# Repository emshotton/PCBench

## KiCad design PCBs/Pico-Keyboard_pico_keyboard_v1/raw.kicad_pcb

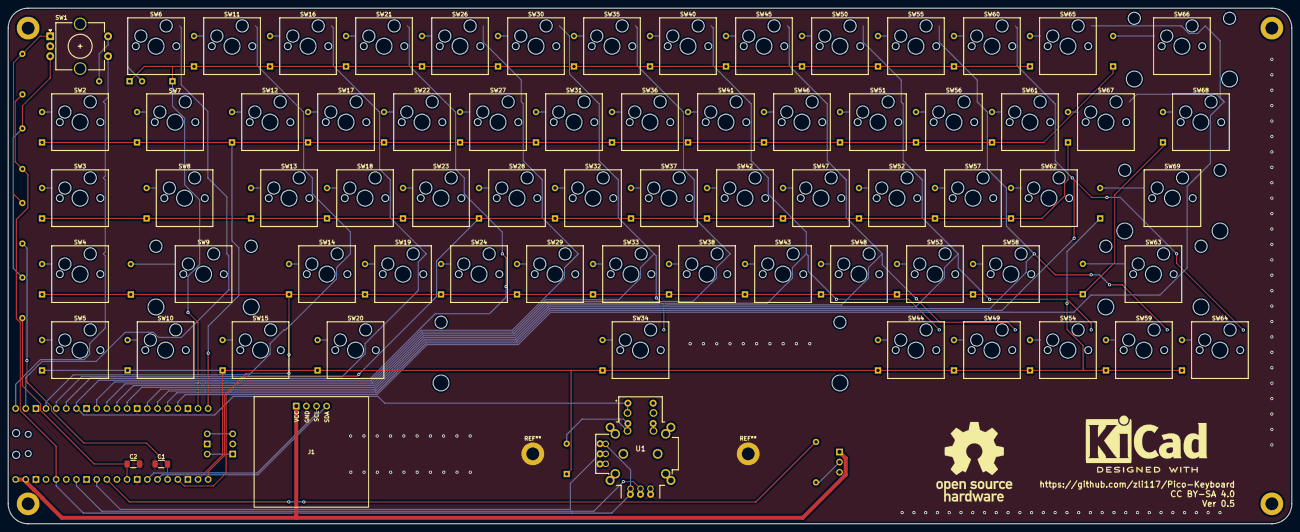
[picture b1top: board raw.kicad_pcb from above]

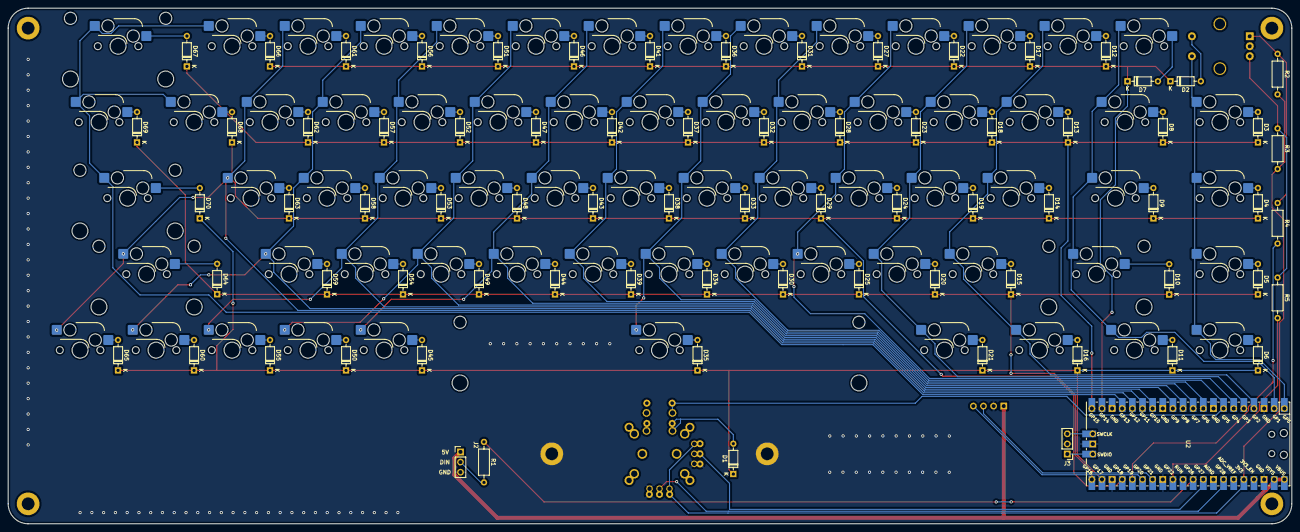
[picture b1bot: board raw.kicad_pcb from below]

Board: 2 copper layers, 321.8 x 129.2 mm, 147 parts (76 on the bottom side), 102 nets.

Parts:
C1, C2: 0.01 μF; C_1206_3216Metric_Pad1.33x1.80mm_HandSolder
D1, D2, D3, D4, D5, D6, D7, D8, D9, D10, D11, D12, D13, D14, D15, D16, D17, D18, D19, D20, D21, D22, D23, D24, D25, D27, D28, D29, D30, D31, D32, D33, D34, D35, D36, D37, D38, D39, D41, D42, D43, D44, D45, D46, D47, D48, D49, D50, D51, D52, D53, D54, D55, D56, D57, D58, D59, D60, D61, D62, D63, D64, D65, D66, D67, D68, D69, D70: D; D_DO-35_SOD27_P7.62mm_Horizontal
J1: Conn_01x04_12864; JMD0.96C
J2, J3: Conn_01x03_Female; PinHeader_1x03_P2.54mm_Vertical
R1: 330; R_Axial_DIN0207_L6.3mm_D2.5mm_P10.16mm_Horizontal
R2, R3, R4, R5: 10k; R_Axial_DIN0207_L6.3mm_D2.5mm_P10.16mm_Horizontal
SW1: RotaryEncoder_Switch; RotaryEncoder_Alps_EC11E-Switch_Vertical_H20mm_CircularMoun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
SW2: SW_esc; SW_Hotswap_Kailh_MX_1.00u
SW3: SW_del; SW_Hotswap_Kailh_MX_1.00u
SW4: SW_ins; SW_Hotswap_Kailh_MX_1.00u
SW5: SW_fn1; SW_Hotswap_Kailh_MX_1.00u
SW6: SW_`; SW_Hotswap_Kailh_MX_1.00u
SW7: SW_tab; SW_Hotswap_Kailh_MX_1.50u
SW8: SW_caps; SW_Hotswap_Kailh_MX_1.75u
SW9: SW_shift; SW_Hotswap_Kailh_MX_2.25u
SW10: SW_ctrl; SW_Hotswap_Kailh_MX_1.25u
SW11: SW_1; SW_Hotswap_Kailh_MX_1.00u
SW12: SW_q; SW_Hotswap_Kailh_MX_1.00u
SW13: SW_a; SW_Hotswap_Kailh_MX_1.00u
SW14: SW_z; SW_Hotswap_Kailh_MX_1.00u
SW15: SW_super; SW_Hotswap_Kailh_MX_1.25u
SW16: SW_2; SW_Hotswap_Kailh_MX_1.00u
SW17: SW_w; SW_Hotswap_Kailh_MX_1.00u
SW18: SW_s; SW_Hotswap_Kailh_MX_1.00u
SW19: SW_x; SW_Hotswap_Kailh_MX_1.00u
SW20: SW_alt; SW_Hotswap_Kailh_MX_1.25u
SW21: SW_3; SW_Hotswap_Kailh_MX_1.00u
SW22: SW_e; SW_Hotswap_Kailh_MX_1.00u
SW23: SW_d; SW_Hotswap_Kailh_MX_1.00u
SW24: SW_c; SW_Hotswap_Kailh_MX_1.00u
SW26: SW_4; SW_Hotswap_Kailh_MX_1.00u
SW27: SW_r; SW_Hotswap_Kailh_MX_1.00u
SW28: SW_f; SW_Hotswap_Kailh_MX_1.00u
SW29: SW_v; SW_Hotswap_Kailh_MX_1.00u
SW30: SW_5; SW_Hotswap_Kailh_MX_1.00u
SW31: SW_t; SW_Hotswap_Kailh_MX_1.00u
SW32: SW_g; SW_Hotswap_Kailh_MX_1.00u
SW33: SW_b; SW_Hotswap_Kailh_MX_1.00u
SW34: SW_space; SW_Hotswap_Kailh_MX_6.25u
SW35: SW_6; SW_Hotswap_Kailh_MX_1.00u
SW36: SW_y; SW_Hotswap_Kailh_MX_1.00u
SW37: SW_h; SW_Hotswap_Kailh_MX_1.00u
SW38: SW_n; SW_Hotswap_Kailh_MX_1.00u
SW40: SW_7; SW_Hotswap_Kailh_MX_1.00u
SW41: SW_u; SW_Hotswap_Kailh_MX_1.00u
SW42: SW_j; SW_Hotswap_Kailh_MX_1.00u
SW43: SW_m; SW_Hotswap_Kailh_MX_1.00u
SW44: SW_fn2; SW_Hotswap_Kailh_MX_1.00u
SW45: SW_8; SW_Hotswap_Kailh_MX_1.00u
SW46: SW_i; SW_Hotswap_Kailh_MX_1.00u
SW47: SW_k; SW_Hotswap_Kailh_MX_1.00u
SW48: SW_,; SW_Hotswap_Kailh_MX_1.00u
SW49: SW_left; SW_Hotswap_Kailh_MX_1.00u
SW50: SW_9; SW_Hotswap_Kailh_MX_1.00u
SW51: SW_o; SW_Hotswap_Kailh_MX_1.00u
SW52: SW_l; SW_Hotswap_Kailh_MX_1.00u
SW53: SW_.; SW_Hotswap_Kailh_MX_1.00u
SW54: SW_down; SW_Hotswap_Kailh_MX_1.00u
SW55: SW_0; SW_Hotswap_Kailh_MX_1.00u
SW56: SW_p; SW_Hotswap_Kailh_MX_1.00u
SW57: SW_;; SW_Hotswap_Kailh_MX_1.00u
SW58: SW_/; SW_Hotswap_Kailh_MX_1.00u
SW59: SW_up; SW_Hotswap_Kailh_MX_1.00u
SW60: SW_-; SW_Hotswap_Kailh_MX_1.00u
SW61: SW_[; SW_Hotswap_Kailh_MX_1.00u
SW62: SW_'; SW_Hotswap_Kailh_MX_1.00u
SW63: SW_r_shift; SW_Hotswap_Kailh_MX_2.75u
SW64: SW_right; SW_Hotswap_Kailh_MX_1.00u
SW65: SW_+; SW_Hotswap_Kailh_MX_1.00u
SW66: SW_back; SW_Hotswap_Kailh_MX_2.00u
SW67: SW_]; SW_Hotswap_Kailh_MX_1.00u
SW68: SW_\; SW_Hotswap_Kailh_MX_1.50u
SW69: SW_enter; SW_Hotswap_Kailh_MX_2.25u
U1: RKJXV1224; RKJXV122400R_COM09032
U2: Pico; RPi_Pico_SMD_TH

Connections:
+3V3: R2.2, R3.2, U1.A11 (V+), U1.B11 (H+), U2.36 (3V3)
+5V: J1.1, J2.1, U2.39 (VSYS), U2.40 (VBUS)
C0: SW1.S1, SW2.2 (B), SW3.2 (B), SW4.2 (B), SW5.2 (B), U2.1 (GPIO0)
C1: SW6.2 (B), SW7.2 (B), SW8.2 (B), SW9.2 (B), SW10.2 (B), U2.2 (GPIO1)
C2: SW11.2 (B), SW12.2 (B), SW13.2 (B), SW14.2 (B), SW15.2 (B), U2.4 (GPIO2)
C3: SW16.2 (B), SW17.2 (B), SW18.2 (B), SW19.2 (B), SW20.2 (B), U2.5 (GPIO3)
C4: SW21.2 (B), SW22.2 (B), SW23.2 (B), SW24.2 (B), U2.6 (GPIO4)
C5: SW26.2 (B), SW27.2 (B), SW28.2 (B), SW29.2 (B), U1.D1 (SEL-), U2.7 (GPIO5)
C6: SW30.2 (B), SW31.2 (B), SW32.2 (B), SW33.2 (B), SW34.2 (B), U2.9 (GPIO6)
C7: SW35.2 (B), SW36.2 (B), SW37.2 (B), SW38.2 (B), U2.10 (GPIO7)
C8: SW40.2 (B), SW41.2 (B), SW42.2 (B), SW43.2 (B), SW44.2 (B), U2.11 (GPIO8)
C9: SW45.2 (B), SW46.2 (B), SW47.2 (B), SW48.2 (B), SW49.2 (B), U2.12 (GPIO9)
C10: SW50.2 (B), SW51.2 (B), SW52.2 (B), SW53.2 (B), SW54.2 (B), U2.14 (GPIO10)
C11: SW55.2 (B), SW56.2 (B), SW57.2 (B), SW58.2 (B), SW59.2 (B), U2.15 (GPIO11)
C12: SW60.2 (B), SW61.2 (B), SW62.2 (B), SW63.2 (B), SW64.2 (B), U2.16 (GPIO12)
C13: SW65.2 (B), SW66.2 (B), SW67.2 (B), SW68.2 (B), SW69.2 (B), U2.17 (GPIO13)
GND: C1.1, C2.2, J1.2, J2.3, J3.2, SW1.C, U1.A13 (V-), U1.B13 (H-), U2.3 (GND), U2.8 (GND), U2.13 (GND), U2.18 (GND), U2.23 (GND), U2.28 (GND), U2.38 (GND), U2.42 (GND)
GPIO14: D2.1 (K), D7.1 (K), D12.1 (K), D17.1 (K), D22.1 (K), D27.1 (K), D31.1 (K), D36.1 (K), D41.1 (K), D46.1 (K), D51.1 (K), D56.1 (K), D61.1 (K), D66.1 (K), U2.19 (GPIO14)
GPIO15: D3.1 (K), D8.1 (K), D13.1 (K), D18.1 (K), D23.1 (K), D28.1 (K), D32.1 (K), D37.1 (K), D42.1 (K), D47.1 (K), D52.1 (K), D57.1 (K), D62.1 (K), D67.1 (K), U2.20 (GPIO15)
GPIO16: D5.1 (K), D10.1 (K), D15.1 (K), D20.1 (K), D25.1 (K), D30.1 (K), D34.1 (K), D39.1 (K), D44.1 (K), D49.1 (K), D54.1 (K), D59.1 (K), D64.1 (K), D69.1 (K), U2.21 (GPIO16)
GPIO17: D1.1 (K), D6.1 (K), D11.1 (K), D16.1 (K), D21.1 (K), D35.1 (K), D45.1 (K), D50.1 (K), D55.1 (K), D60.1 (K), D65.1 (K), D70.1 (K), U2.22 (GPIO17)
GPIO18: D4.1 (K), D9.1 (K), D14.1 (K), D19.1 (K), D24.1 (K), D29.1 (K), D33.1 (K), D38.1 (K), D43.1 (K), D48.1 (K), D53.1 (K), D58.1 (K), D63.1 (K), D68.1 (K), U2.24 (GPIO18)
GPIO19: C1.2, R4.2, U2.25 (GPIO19)
GPIO20: J1.4, U2.26 (GPIO20)
GPIO21: J1.3, U2.27 (GPIO21)
GPIO22: C2.1, R5.2, U2.29 (GPIO22)
GPIO26: R1.1, U2.31 (GPIO26_ADC0)
GPIO27: U1.A12 (V), U2.32 (GPIO27_ADC1)
GPIO28: U1.B12 (H), U2.34 (GPIO28_ADC2)
unnamed: D1.2 (A), U1.C1 (SEL+)
unnamed: D2.2 (A), SW1.S2
unnamed: D3.2 (A), SW2.1 (A)
unnamed: D4.2 (A), SW3.1 (A)
unnamed: D5.2 (A), SW4.1 (A)
unnamed: D6.2 (A), SW5.1 (A)
unnamed: D7.2 (A), SW6.1 (A)
unnamed: D8.2 (A), SW7.1 (A)
unnamed: D9.2 (A), SW8.1 (A)
unnamed: D10.2 (A), SW9.1 (A)
unnamed: D11.2 (A), SW10.1 (A)
unnamed: D12.2 (A), SW11.1 (A)
unnamed: D13.2 (A), SW12.1 (A)
unnamed: D14.2 (A), SW13.1 (A)
unnamed: D15.2 (A), SW14.1 (A)
unnamed: D16.2 (A), SW15.1 (A)
unnamed: D17.2 (A), SW16.1 (A)
unnamed: D18.2 (A), SW17.1 (A)
unnamed: D19.2 (A), SW18.1 (A)
unnamed: D20.2 (A), SW19.1 (A)
unnamed: D21.2 (A), SW20.1 (A)
unnamed: D22.2 (A), SW21.1 (A)
unnamed: D23.2 (A), SW22.1 (A)
unnamed: D24.2 (A), SW23.1 (A)
unnamed: D25.2 (A), SW24.1 (A)
unnamed: D27.2 (A), SW26.1 (A)
unnamed: D28.2 (A), SW27.1 (A)
unnamed: D29.2 (A), SW28.1 (A)
unnamed: D30.2 (A), SW29.1 (A)
unnamed: D31.2 (A), SW30.1 (A)
unnamed: D32.2 (A), SW31.1 (A)
unnamed: D33.2 (A), SW32.1 (A)
unnamed: D34.2 (A), SW33.1 (A)
unnamed: D35.2 (A), SW34.1 (A)
unnamed: D36.2 (A), SW35.1 (A)
unnamed: D37.2 (A), SW36.1 (A)
unnamed: D38.2 (A), SW37.1 (A)
unnamed: D39.2 (A), SW38.1 (A)
unnamed: D41.2 (A), SW40.1 (A)
unnamed: D42.2 (A), SW41.1 (A)
unnamed: D43.2 (A), SW42.1 (A)
unnamed: D44.2 (A), SW43.1 (A)
unnamed: D45.2 (A), SW44.1 (A)
unnamed: D46.2 (A), SW45.1 (A)
unnamed: D47.2 (A), SW46.1 (A)
unnamed: D48.2 (A), SW47.1 (A)
unnamed: D49.2 (A), SW48.1 (A)
unnamed: D50.2 (A), SW49.1 (A)
unnamed: D51.2 (A), SW50.1 (A)
unnamed: D52.2 (A), SW51.1 (A)
unnamed: D53.2 (A), SW52.1 (A)
unnamed: D54.2 (A), SW53.1 (A)
unnamed: D55.2 (A), SW54.1 (A)
unnamed: D56.2 (A), SW55.1 (A)
unnamed: D57.2 (A), SW56.1 (A)
unnamed: D58.2 (A), SW57.1 (A)
unnamed: D59.2 (A), SW58.1 (A)
unnamed: D60.2 (A), SW59.1 (A)
unnamed: D61.2 (A), SW60.1 (A)
unnamed: D62.2 (A), SW61.1 (A)
unnamed: D63.2 (A), SW62.1 (A)
unnamed: D64.2 (A), SW63.1 (A)
unnamed: D65.2 (A), SW64.1 (A)
unnamed: D66.2 (A), SW65.1 (A)
unnamed: D67.2 (A), SW66.1 (A)
unnamed: D68.2 (A), SW67.1 (A)
unnamed: D69.2 (A), SW68.1 (A)
unnamed: D70.2 (A), SW69.1 (A)
unnamed: J2.2, R1.2
unnamed: J3.1, U2.43 (SWDIO)
unnamed: J3.3, U2.41 (SWCLK)
unnamed: R2.1, R4.1, SW1.A
unnamed: R3.1, R5.1, SW1.B

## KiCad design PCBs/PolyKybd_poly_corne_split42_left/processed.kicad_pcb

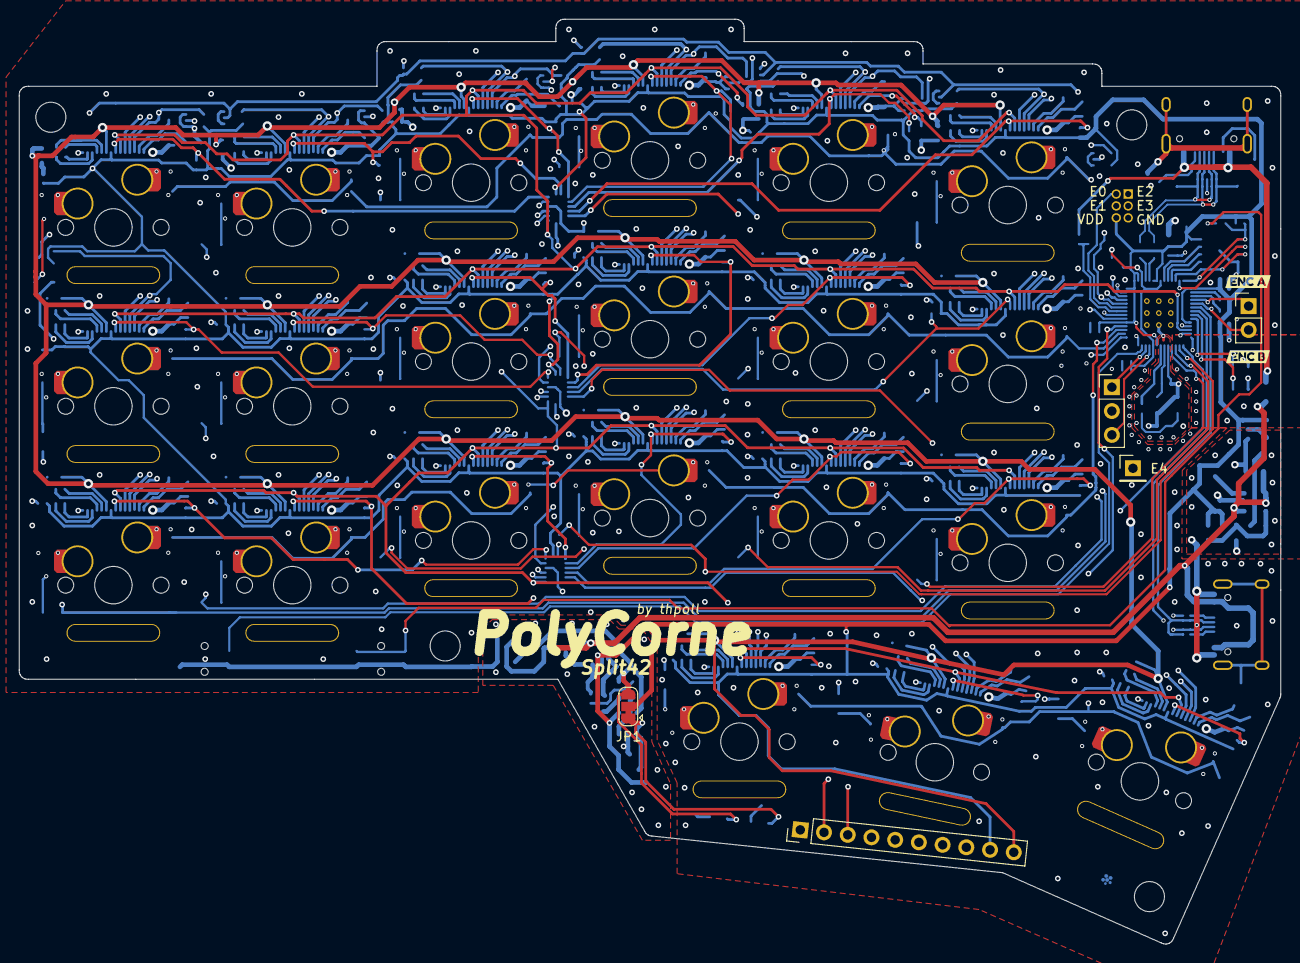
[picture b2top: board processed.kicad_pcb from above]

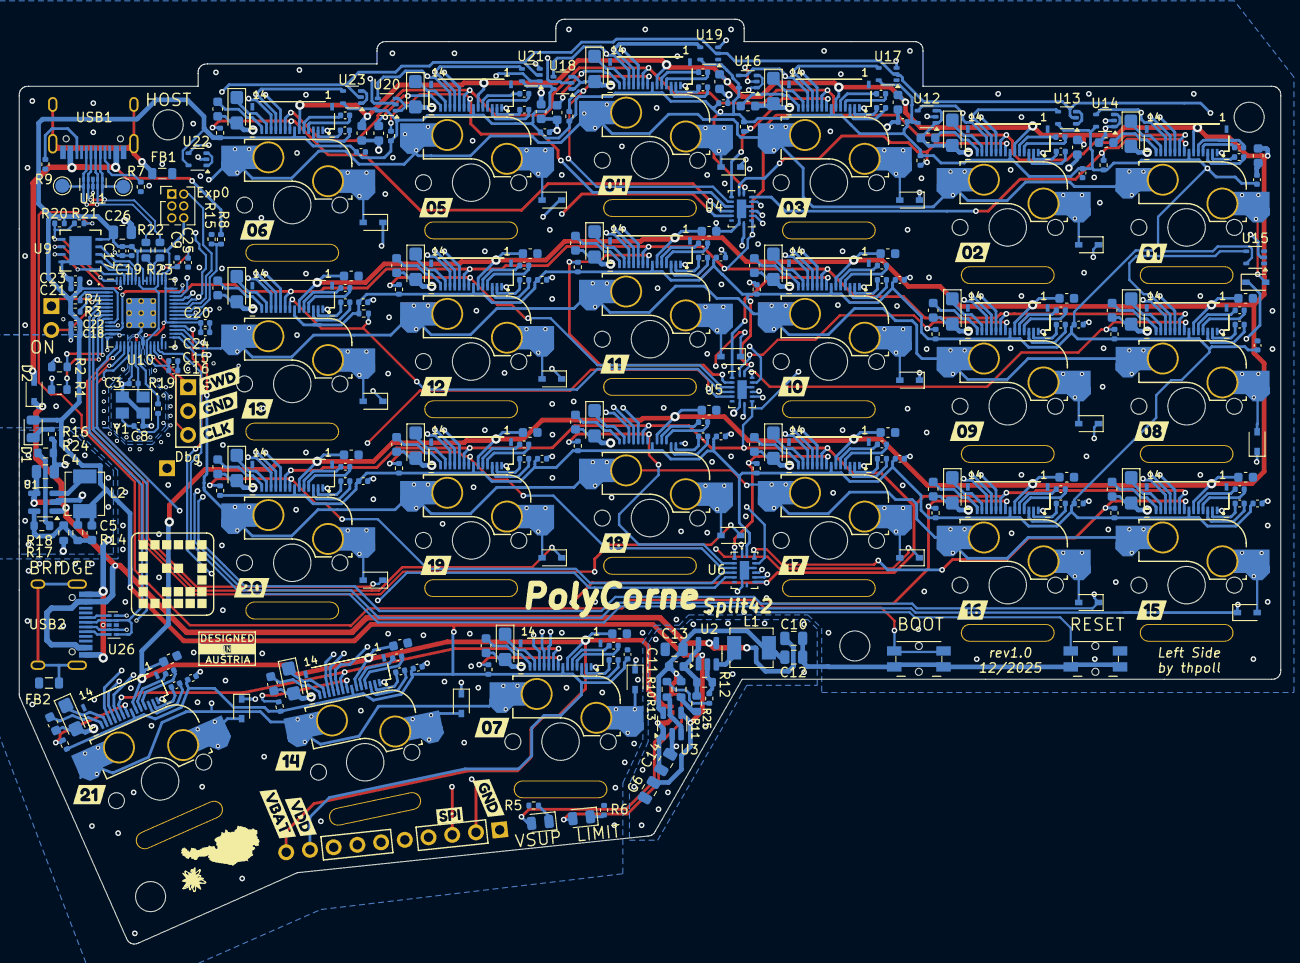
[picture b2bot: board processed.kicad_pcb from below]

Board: 4 copper layers, 134.3 x 98.5 mm, 330 parts (302 on the bottom side), 247 nets.

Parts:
C1_1, C1_2, C1_3, C1_4, C1_5, C1_6, C1_8, C1_9, C1_10, C1_11, C1_12, C1_13, C1_15, C1_16, C1_17, C1_18, C1_19, C1_20, C1_25, C1_26, C1_27: 2.2uF 0603 25V; C_0603_1608Metric
C2_1, C2_2, C2_3, C2_4, C2_5, C2_6, C2_8, C2_9, C2_10, C2_11, C2_12, C2_13, C2_15, C2_16, C2_17, C2_18, C2_19, C2_20, C2_25, C2_26, C2_27: 2.2uF 0603 16V; C_0603_1608Metric
C3, C8: 27pF 0402 16V; C_0402_1005Metric
C3_1, C3_2, C3_3, C3_4, C3_5, C3_6, C3_8, C3_9, C3_10, C3_11, C3_12, C3_13, C3_15, C3_16, C3_17, C3_18, C3_19, C3_20, C3_25, C3_26, C3_27, C5_1, C5_2, C5_3, C5_4, C5_5, C5_6, C5_8, C5_9, C5_10, C5_11, C5_12, C5_13, C5_15, C5_16, C5_17, C5_18, C5_19, C5_20, C5_25, C5_26, C5_27, C6_1, C6_2, C6_3, C6_4, C6_5, C6_6, C6_8, C6_9, C6_10, C6_11, C6_12, C6_13, C6_15, C6_16, C6_17, C6_18, C6_19, C6_20, C6_25, C6_26, C6_27, C24, C25: 1uF 0402 16V; C_0402_1005Metric
C4, C10: 4.7uF 0805 25V; C_0805_2012Metric
C4_1, C4_2, C4_3, C4_4, C4_5, C4_6, C4_8, C4_9, C4_10, C4_11, C4_12, C4_13, C4_15, C4_16, C4_17, C4_18, C4_19, C4_20, C4_25, C4_26, C4_27: 4.7uF 3216 25V Tantalum; CP_EIA-3216-18_Kemet-A
C5, C11: 6.8pF 0603 50V; C_0603_1608Metric
C6, C12, C13, C14, C26: 10uF 0805 16V; C_0805_2012Metric
C9, C15, C16, C17, C18, C19, C20, C21, C22, C23: 100nF 0402 16V; C_0402_1005Metric
D1: Red 0805 C84256; LED_0805_2012Metric
D1_1, D1_2, D1_3, D1_4, D1_5, D1_6, D1_8, D1_9, D1_10, D1_11, D1_12, D1_13, D1_15, D1_16, D1_17, D1_18, D1_19, D1_20, D1_25, D1_26, D1_27: 1N4148WSX; D_SOD-323Ext
D2: 1N5819WS; D_SOD-323Ext
D5: Green 0805 C2297; LED_0805_2012Metric
D6: Yellow 0805 C2296; LED_0805_2012Metric
DBG1: Conn_01x03_Male; PinHeader_1x03_P2.54mm_Vertical
DBG3: DebugPort; PinHeader_1x10_P2.54mm_Vertical
Enc0: Conn_01x02; PinHeader_1x02_P2.54mm_Vertical
Exp0: Conn_02x03; PinHeader_2x03_P1.27mm_Vertical
Exp1: Conn_01x01; PinHeader_1x01_P2.54mm_Vertical
FB1, FB2: GZ2012D601TF; L_0805_2012Metric
J1, J2, J3, J4, J5, J6, J8, J9, J10, J11, J12, J13, J15, J16, J17, J19, J20, J25, J26, J27: FH34SRJ-14S-0.5SH; FH34SRJ14S05SH50-Rev2
JP1: CurrentLimitBypass; SolderJumper-3_P1.3mm_Bridged12_RoundedPad1.0x1.5mm
L1, L2: 2.2uH; SMMS0420-2R2M
R1, R2: 22 0603; R_0603_1608Metric
R1_1, R1_2, R1_3, R1_4, R1_5, R1_6, R1_8, R1_9, R1_10, R1_11, R1_12, R1_13, R1_15, R1_16, R1_17, R1_18, R1_19, R1_20, R1_25, R1_26, R1_27, R15, R20, R25: 10k 0402; R_0402_1005Metric
R3, R4, R7, R9: 5.1K 0402; R_0402_1005Metric
R5, R6, R16, R19, R21: 1k 0402; R_0402_1005Metric
R8: 5.6K 0402; R_0402_1005Metric
R10, R11: 390k 0603 1%; R_0603_1608Metric
R12, R17: 150k 0603; R_0603_1608Metric
R13: 12k 0603; R_0603_1608Metric
R14: 680k 0603; R_0603_1608Metric
R18: 10M 0603; R_0603_1608Metric
R22, R23: 27 0603; R_0603_1608Metric
R24: 2M2 0603; R_0603_1608Metric
SW2, SW3: EVQPUC02K; Panasonic_EVQPUL_EVQPUC
SW_K_1, SW_K_2, SW_K_3, SW_K_4, SW_K_5, SW_K_6, SW_K_7, SW_K_8, SW_K_9, SW_K_10, SW_K_11, SW_K_12, SW_K_13, SW_K_14, SW_K_15, SW_K_16, SW_K_17, SW_K_18, SW_K_19, SW_K_20, SW_K_21: Kailh CPG151101S11-16; Kailh_socket_MX_Indicators
TP1: USB_D-; TestPoint_Pad_D1.5mm
TP14: USB_D+; TestPoint_Pad_D1.5mm
U1, U2: TLV62569DBVR; SOT-23-5
U3: SY6280AAC; SOT-23-5
U4, U5, U6: 74HC595BQ; Nexperia 74HC595BQ DHVQFN16
U9: W25Q64JVXGIM; DFN_XGIQ TR_WIN
U10: RP2040; RP2040-QFN-56
U11, U26: TPD4E05U06DQAR; USON-10
U12, U13, U14, U15, U16, U17, U18, U19, U20, U21, U22, U23: 74AHC1G125GW,125; SOT-353_SC-70-5_Slim
USB1, USB2: TYPE-C-31-M-12; HRO-TYPE-C-31-M-12-Assembly
Y1: 7M12000044; Crystal_SMD_3225-4Pin_3.2x2.5mm
kibuzzard-63EB51FD: G***; kibuzzard-63EB51FD
kibuzzard-639C2A93: G***; kibuzzard-639C2A93
kibuzzard-639C2D09: G***; kibuzzard-639C2D09
kibuzzard-639C2D25: G***; kibuzzard-639C2D25
kibuzzard-639C28BB, kibuzzard-639C28BB#2: G***; kibuzzard-639C28BB
kibuzzard-639C28CF: G***; kibuzzard-639C28CF
kibuzzard-639C34D4: G***; kibuzzard-639C34D4
kibuzzard-639C34FD: G***; kibuzzard-639C34FD
kibuzzard-639C35A2: G***; kibuzzard-639C35A2
kibuzzard-639C35AF: G***; kibuzzard-639C35AF
kibuzzard-639C35B8: G***; kibuzzard-639C35B8
kibuzzard-639C35C3: G***; kibuzzard-639C35C3
kibuzzard-639C35CB: G***; kibuzzard-639C35CB
kibuzzard-639C35DA: G***; kibuzzard-639C35DA
kibuzzard-639C35E7: G***; kibuzzard-639C35E7
kibuzzard-639C39A5: G***; kibuzzard-639C39A5
kibuzzard-639C294B: G***; kibuzzard-639C294B
kibuzzard-639C352E: G***; kibuzzard-639C352E
kibuzzard-639C353A: G***; kibuzzard-639C353A
kibuzzard-639C355D: G***; kibuzzard-639C355D
kibuzzard-639C357F: G***; kibuzzard-639C357F
kibuzzard-639C358A: G***; kibuzzard-639C358A
kibuzzard-639C3508: G***; kibuzzard-639C3508
kibuzzard-639C3514: G***; kibuzzard-639C3514
kibuzzard-639C3522: G***; kibuzzard-639C3522
kibuzzard-639C3548: G***; kibuzzard-639C3548
kibuzzard-639C3550: G***; kibuzzard-639C3550
kibuzzard-639C3575: G***; kibuzzard-639C3575
kibuzzard-639C3594: G***; kibuzzard-639C3594

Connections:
+1V1: C15.1, C16.1, C25.1, U10.23 (DVDD), U10.45 (VREG_VOUT), U10.50 (DVDD)
/K_1/C1N: C6_2.2, J2.5
/K_1/C1P: C6_2.1, J2.4
/K_1/C2N: C5_2.2, J2.3
/K_1/C2P: C5_2.1, J2.2
/K_1/CS: J2.8, R1_2.2, U4.1 (QB)
/K_1/VCC: C1_2.1, J2.14
/K_1/VCOMH: C4_2.1, J2.13
/K_2/C1N: C6_3.2, J3.5
/K_2/C1P: C6_3.1, J3.4
/K_2/C2N: C5_3.2, J3.3
/K_2/C2P: C5_3.1, J3.2
/K_2/CS: J3.8, R1_3.2, U4.2 (QC)
/K_2/VCC: C1_3.1, J3.14
/K_2/VCOMH: C4_3.1, J3.13
/K_3/C1N: C6_4.2, J4.5
/K_3/C1P: C6_4.1, J4.4
/K_3/C2N: C5_4.2, J4.3
/K_3/C2P: C5_4.1, J4.2
/K_3/CS: J4.8, R1_4.2, U4.3 (QD)
/K_3/VCC: C1_4.1, J4.14
/K_3/VCOMH: C4_4.1, J4.13
/K_4/C1N: C6_5.2, J5.5
/K_4/C1P: C6_5.1, J5.4
/K_4/C2N: C5_5.2, J5.3
/K_4/C2P: C5_5.1, J5.2
/K_4/CS: J5.8, R1_5.2, U4.4 (QE)
/K_4/VCC: C1_5.1, J5.14
/K_4/VCOMH: C4_5.1, J5.13
/K_5/C1N: C6_6.2, J6.5
/K_5/C1P: C6_6.1, J6.4
/K_5/C2N: C5_6.2, J6.3
/K_5/C2P: C5_6.1, J6.2
/K_5/CS: J6.8, R1_6.2, U4.5 (QF)
/K_5/VCC: C1_6.1, J6.14
/K_5/VCOMH: C4_6.1, J6.13
/K_A/C1N: C6_16.2, J16.5
/K_A/C1P: C6_16.1, J16.4
/K_A/C2N: C5_16.2, J16.3
/K_A/C2P: C5_16.1, J16.2
/K_A/CS: J16.8, R1_16.2, U6.1 (QB)
/K_A/VCC: C1_16.1, J16.14
/K_A/VCOMH: C4_16.1, J16.13
/K_B/C1N: C6_27.2, J27.5
/K_B/C1P: C6_27.1, J27.4
/K_B/C2N: C5_27.2, J27.3
/K_B/C2P: C5_27.1, J27.2
/K_B/CS: J27.8, R1_27.2, U6.6 (QG)
/K_B/VCC: C1_27.1, J27.14
/K_B/VCOMH: C4_27.1, J27.13
/K_C/C1N: C6_25.2, J25.5
/K_C/C1P: C6_25.1, J25.4
/K_C/C2N: C5_25.2, J25.3
/K_C/C2P: C5_25.1, J25.2
/K_C/CS: J25.8, R1_25.2, U4.6 (QG)
/K_C/VCC: C1_25.1, J25.14
/K_C/VCOMH: C4_25.1, J25.13
/K_D/CS: R1_18.2, U6.3 (QD)
/K_E/C1N: C6_11.2, J11.5
/K_E/C1P: C6_11.1, J11.4
/K_E/C2N: C5_11.2, J11.3
/K_E/C2P: C5_11.1, J11.2
/K_E/CS: J11.8, R1_11.2, U5.3 (QD)
/K_E/VCC: C1_11.1, J11.14
/K_E/VCOMH: C4_11.1, J11.13
/K_F/C1N: C6_19.2, J19.5
/K_F/C1P: C6_19.1, J19.4
/K_F/C2N: C5_19.2, J19.3
/K_F/C2P: C5_19.1, J19.2
/K_F/CS: J19.8, R1_19.2, U6.4 (QE)
/K_F/VCC: C1_19.1, J19.14
/K_F/VCOMH: C4_19.1, J19.13
/K_G/C1N: C6_20.2, J20.5
/K_G/C1P: C6_20.1, J20.4
/K_G/C2N: C5_20.2, J20.3
/K_G/C2P: C5_20.1, J20.2
/K_G/CS: J20.8, R1_20.2, U6.5 (QF)
/K_G/VCC: C1_20.1, J20.14
/K_G/VCOMH: C4_20.1, J20.13
/K_L1/C1N: C6_1.2, J1.5
/K_L1/C1P: C6_1.1, J1.4
/K_L1/C2N: C5_1.2, J1.3
/K_L1/C2P: C5_1.1, J1.2
/K_L1/CS: J1.8, R1_1.2, U4.15 (QA)
/K_L1/VCC: C1_1.1, J1.14
/K_L1/VCOMH: C4_1.1, J1.13
/K_L2/C1N: C6_8.2, J8.5
/K_L2/C1P: C6_8.1, J8.4
/K_L2/C2N: C5_8.2, J8.3
/K_L2/C2P: C5_8.1, J8.2
/K_L2/CS: J8.8, R1_8.2, U5.15 (QA)
/K_L2/VCC: C1_8.1, J8.14
/K_L2/VCOMH: C4_8.1, J8.13
/K_L3/C1N: C6_15.2, J15.5
/K_L3/C1P: C6_15.1, J15.4
/K_L3/C2N: C5_15.2, J15.3
/K_L3/C2P: C5_15.1, J15.2
/K_L3/CS: J15.8, R1_15.2, U6.15 (QA)
/K_L3/VCC: C1_15.1, J15.14
/K_L3/VCOMH: C4_15.1, J15.13
/K_Q/C1N: C6_9.2, J9.5
/K_Q/C1P: C6_9.1, J9.4
/K_Q/C2N: C5_9.2, J9.3
/K_Q/C2P: C5_9.1, J9.2
/K_Q/CS: J9.8, R1_9.2, U5.1 (QB)
/K_Q/VCC: C1_9.1, J9.14
/K_Q/VCOMH: C4_9.1, J9.13
/K_R/C1N: C6_12.2, J12.5
/K_R/C1P: C6_12.1, J12.4
/K_R/C2N: C5_12.2, J12.3
/K_R/C2P: C5_12.1, J12.2
/K_R/CS: J12.8, R1_12.2, U5.4 (QE)
/K_R/VCC: C1_12.1, J12.14
/K_R/VCOMH: C4_12.1, J12.13
/K_S/C1N: C6_17.2, J17.5
/K_S/C1P: C6_17.1, J17.4
/K_S/C2N: C5_17.2, J17.3
/K_S/C2P: C5_17.1, J17.2
/K_S/CS: J17.8, R1_17.2, U6.2 (QC)
/K_S/VCC: C1_17.1, J17.14
/K_S/VCOMH: C4_17.1, J17.13
/K_T/C1N: C6_13.2, J13.5
/K_T/C1P: C6_13.1, J13.4
/K_T/C2N: C5_13.2, J13.3
/K_T/C2P: C5_13.1, J13.2
/K_T/CS: J13.8, R1_13.2, U5.5 (QF)
/K_T/VCC: C1_13.1, J13.14
/K_T/VCOMH: C4_13.1, J13.13
/K_V/C1N: C6_26.2, J26.5
/K_V/C1P: C6_26.1, J26.4
/K_V/C2N: C5_26.2, J26.3
/K_V/C2P: C5_26.1, J26.2
/K_V/CS: J26.8, R1_26.2, U5.6 (QG)
/K_V/VCC: C1_26.1, J26.14
/K_V/VCOMH: C4_26.1, J26.13
/K_W/C1N: C6_10.2, J10.5
/K_W/C1P: C6_10.1, J10.4
/K_W/C2N: C5_10.2, J10.3
/K_W/C2P: C5_10.1, J10.2
/K_W/CS: J10.8, R1_10.2, U5.2 (QC)
/K_W/VCC: C1_10.1, J10.14
/K_W/VCOMH: C4_10.1, J10.13
/RpPico/GPIO6: R1.1, U10.8 (GPIO6)
/RpPico/GPIO7: R2.1, U10.9 (GPIO7)
/RpPico/GPIO24: R8.2, R15.1, U10.36 (GPIO24)
/RpPico/QSPI_SCLK: U9.6 (CLK), U10.52 (QSPI_SCLK)
/RpPico/QSPI_SD0: U9.5 (DI(IO0)), U10.53 (QSPI_SD0)
/RpPico/QSPI_SD1: U9.2 (DO(IO1)), U10.55 (QSPI_SD1)
/RpPico/QSPI_SD2: U9.3 (~WP(IO2)), U10.54 (QSPI_SD2)
/RpPico/QSPI_SD3: U9.7 (~HOLD_OR_RESET_(IO3)), U10.51 (QSPI_SD3)
/RpPico/QSPI_SS: R20.2, R21.1, U9.1 (~CS), U10.56 (QSPI_SS)
/RpPico/RUN: SW3.2, U10.26 (RUN)
/RpPico/SWCLK: DBG1.3, U10.24 (SWCLK)
/RpPico/SWD: DBG1.1, U10.25 (SWD)
/RpPico/USB_D+: R22.1, TP14.1, U11.1 (IO1), U11.4 (D2+), U11.7 (NC), U11.10 (NC), USB1.6 (DP1), USB1.8 (DP2)
/RpPico/USB_D-: R23.1, TP1.1, U11.2 (IO2), U11.5 (D2-), U11.6 (NC), U11.9 (NC), USB1.5 (DN2), USB1.7 (DN1)
/RpPico/XIN: C3.2, U10.20 (XIN), Y1.1
/RpPico/XOUT: R19.2, U10.21 (XOUT)
/RpPico/~USB_BOOT: R21.2, SW2.2
/SCLK1: J1.11, J8.11, J15.11, U15.4 (B)
/SCLK2: J2.11, J9.11, J16.11, U13.4 (B)
/SCLK3: J3.11, J10.11, J17.11, U17.4 (B)
/SCLK4: J4.11, J11.11, J25.11, U19.4 (B)
/SCLK5: J5.11, J12.11, J19.11, J26.11, U21.4 (B)
/SCLK6: J6.11, J13.11, J20.11, J27.11, U23.4 (B)
/SDIN1: J1.12, J8.12, J15.12, U14.4 (B)
/SDIN2: J2.12, J9.12, J16.12, U12.4 (B)
/SDIN3: J3.12, J10.12, J17.12, U16.4 (B)
/SDIN4: J4.12, J11.12, J25.12, U18.4 (B)
/SDIN5: J5.12, J12.12, J19.12, J26.12, U20.4 (B)
/SDIN6: J6.12, J13.12, J20.12, J27.12, U22.4 (B)
/ShiftRegisters/Carry1: U4.9 (QH'), U5.14 (SER)
/ShiftRegisters/Carry2: U5.9 (QH'), U6.14 (SER)
Col1: D1_1.1 (K), D1_8.1 (K), D1_15.1 (K), U10.13 (GPIO10)
Col2: D1_2.1 (K), D1_9.1 (K), D1_16.1 (K), U10.14 (GPIO11)
Col3: D1_3.1 (K), D1_10.1 (K), D1_17.1 (K), U10.15 (GPIO12)
Col4: D1_4.1 (K), D1_11.1 (K), D1_18.1 (K), D1_25.1 (K), U10.16 (GPIO13)
Col5: D1_5.1 (K), D1_12.1 (K), D1_19.1 (K), D1_26.1 (K), U10.17 (GPIO14)
Col6: D1_6.1 (K), D1_13.1 (K), D1_20.1 (K), D1_27.1 (K), U10.18 (GPIO15)
D-C: DBG3.4, J1.10, J2.10, J3.10, J4.10, J5.10, J6.10, J8.10, J9.10, J10.10, J11.10, J12.10, J13.10, J15.10, J16.10, J17.10, J19.10, J20.10, J25.10, J26.10, J27.10, U10.11 (GPIO8)
E0: Exp0.2 (+12V), U10.37 (GPIO25)
E1: Exp0.4 (GND), U10.41 (GPIO29_ADC3)
E2: Exp0.1 (+12V), U10.27 (GPIO16)
E3: Exp0.3 (GND), U10.35 (GPIO23)
E4: Exp1.1, U10.34 (GPIO22)
ENC_A: Enc0.1, U10.4 (GPIO2)
ENC_B: Enc0.2, U10.5 (GPIO3)
GND: C1_1.2, C1_2.2, C1_3.2, C1_4.2, C1_5.2, C1_6.2, C1_8.2, C1_9.2, C1_10.2, C1_11.2, C1_12.2, C1_13.2, C1_15.2, C1_16.2, C1_17.2, C1_18.2, C1_19.2, C1_20.2, C1_25.2, C1_26.2, C1_27.2, C2_1.2, C2_2.2, C2_3.2, C2_4.2, C2_5.2, C2_6.2, C2_8.2, C2_9.2, C2_10.2, C2_11.2, C2_12.2, C2_13.2, C2_15.2, C2_16.2, C2_17.2, C2_18.2, C2_19.2, C2_20.2, C2_25.2, C2_26.2, C2_27.2, C3.1, C3_1.2, C3_2.2, C3_3.2, C3_4.2, C3_5.2, C3_6.2, C3_8.2, C3_9.2, C3_10.2, C3_11.2, C3_12.2, C3_13.2, C3_15.2, C3_16.2, C3_17.2, C3_18.2, C3_19.2, C3_20.2, C3_25.2, C3_26.2, C3_27.2, C4.2, C4_1.2, C4_2.2, C4_3.2, C4_4.2, C4_5.2, C4_6.2, C4_8.2, C4_9.2, C4_10.2, C4_11.2, C4_12.2, C4_13.2, C4_15.2, C4_16.2, C4_17.2, C4_18.2, C4_19.2, C4_20.2, C4_25.2, C4_26.2, C4_27.2, C6.2, C8.1, C9.2, C10.2, C12.2, C13.2, C14.2, C15.2, C16.2, C17.2, C18.2, C19.2, C20.2, C21.2, C22.2, C23.2, C24.2, C25.2, C26.2, DBG1.2, DBG3.1, Exp0.5 (GND), FB1.2, FB2.2, J1.1, J2.1, J3.1, J4.1, J5.1, J6.1, J8.1, J9.1, J10.1, J11.1, J12.1, J13.1, J15.1, J16.1, J17.1, J19.1, J20.1, J25.1, J26.1, J27.1, R5.1, R6.1, R7.1, R9.1, R12.1, R15.2, R16.1, R17.1, R24.2, R25.1, SW2.1, SW3.1, SW_K_1.3 (C), SW_K_2.3 (C), SW_K_3.3 (C), SW_K_4.3 (C), SW_K_5.3 (C), SW_K_6.3 (C), SW_K_7.3 (C), SW_K_8.3 (C), SW_K_9.3 (C), SW_K_10.3 (C), SW_K_11.3 (C), SW_K_12.3 (C), SW_K_13.3 (C), SW_K_14.3 (C), SW_K_15.3 (C), SW_K_16.3 (C), SW_K_17.3 (C), SW_K_18.3 (C), SW_K_19.3 (C), SW_K_20.3 (C), SW_K_21.3 (C), U1.2 (GND), U2.2 (GND), U3.2 (GND), U4.8 (GND), U4.13 (~OE), U4.17 (EP), U5.8 (GND), U5.13 (~OE), U5.17 (EP), U6.8 (GND), U6.13 (~OE), U6.17 (EP), U9.4 (GND), U9.9 (EP), U10.19 (TESTEN), U10.57 (GND), U11.3 (GND), U11.8 (GND), U12.1 (VCCA), U12.3 (GND), U13.1 (VCCA), U13.3 (GND), U14.1 (VCCA), U14.3 (GND), U15.1 (VCCA), U15.3 (GND), U16.1 (VCCA), U16.3 (GND), U17.1 (VCCA), U17.3 (GND), U18.1 (VCCA), U18.3 (GND), U19.1 (VCCA), U19.3 (GND), U20.1 (VCCA), U20.3 (GND), U21.1 (VCCA), U21.3 (GND), U22.1 (VCCA), U22.3 (GND), U23.1 (VCCA), U23.3 (GND), U26.3 (GND), U26.8 (GND), USB1.1 (GND), USB1.12 (GND), USB2.1 (GND), USB2.3 (SBU2), USB2.4 (CC1), USB2.9 (SBU1), USB2.10 (CC2), USB2.12 (GND), Y1.2, Y1.4
I2C_SCL: R3.2, U10.3 (GPIO1)
I2C_SDA: R4.2, U10.2 (GPIO0)
unnamed: C8.2, R19.1, Y1.3
unnamed: D1.1 (K), R16.2
unnamed: D1_1.2 (A), SW_K_1.2 (B)
unnamed: D1_2.2 (A), SW_K_2.2 (B)
unnamed: D1_3.2 (A), SW_K_3.2 (B)
unnamed: D1_4.2 (A), SW_K_4.2 (B)
unnamed: D1_5.2 (A), SW_K_5.2 (B)
unnamed: D1_6.2 (A), SW_K_6.2 (B)
unnamed: D1_8.2 (A), SW_K_8.2 (B)
unnamed: D1_9.2 (A), SW_K_9.2 (B)
unnamed: D1_10.2 (A), SW_K_10.2 (B)
unnamed: D1_11.2 (A), SW_K_11.2 (B)
unnamed: D1_12.2 (A), SW_K_12.2 (B)
unnamed: D1_13.2 (A), SW_K_13.2 (B)
unnamed: D1_15.2 (A), SW_K_15.2 (B)
unnamed: D1_16.2 (A), SW_K_16.2 (B)
unnamed: D1_17.2 (A), SW_K_17.2 (B)
unnamed: D1_18.2 (A), SW_K_18.2 (B)
unnamed: D1_19.2 (A), SW_K_19.2 (B)
unnamed: D1_20.2 (A), SW_K_20.2 (B)
unnamed: D1_25.2 (A), SW_K_7.2 (B)
unnamed: D1_26.2 (A), SW_K_14.2 (B)
unnamed: D1_27.2 (A), SW_K_21.2 (B)
unnamed: C14.1, D5.2 (A), JP1.1 (A), U3.1 (OUT)
unnamed: D5.1 (K), R5.2
unnamed: D6.1 (K), R6.2
unnamed: R10.1, R11.2
unnamed: R13.2, R25.2
unnamed: R18.2, R24.1
unnamed: C5.2, R14.1, R17.2, R18.1, U1.5 (FB)
unnamed: L2.1, U1.3 (SW)
unnamed: C11.2, R11.1, R12.2, U2.5 (FB)
unnamed: L1.1, U2.3 (SW)
unnamed: R13.1, U3.3 (SET)
unnamed: R23.2, U10.46 (USB_DM)
unnamed: R22.2, U10.47 (USB_DP)
unnamed: R7.2, USB1.4 (CC1)
unnamed: R9.2, USB1.10 (CC2)
unnamed: FB1.1, USB1.13 (SHIELD)
unnamed: FB2.1, USB2.13 (SHIELD)
RESET: DBG3.5, J1.9, J2.9, J3.9, J4.9, J5.9, J6.9, J8.9, J9.9, J10.9, J11.9, J12.9, J13.9, J15.9, J16.9, J17.9, J19.9, J20.9, J25.9, J26.9, J27.9, U4.10 (~SRCLR), U5.10 (~SRCLR), U6.10 (~SRCLR), U10.12 (GPIO9)
Row1: SW_K_1.1 (A), SW_K_2.1 (A), SW_K_3.1 (A), SW_K_4.1 (A), SW_K_5.1 (A), SW_K_6.1 (A), U10.29 (GPIO18)
Row2: SW_K_8.1 (A), SW_K_9.1 (A), SW_K_10.1 (A), SW_K_11.1 (A), SW_K_12.1 (A), SW_K_13.1 (A), U10.30 (GPIO19)
Row3: SW_K_15.1 (A), SW_K_16.1 (A), SW_K_17.1 (A), SW_K_18.1 (A), SW_K_19.1 (A), SW_K_20.1 (A), U10.31 (GPIO20)
Row4: SW_K_7.1 (A), SW_K_14.1 (A), SW_K_21.1 (A), U10.32 (GPIO21)
SCLK_RAW: DBG3.2, R1.2, U13.2 (A), U15.2 (A), U17.2 (A), U19.2 (A), U21.2 (A), U23.2 (A)
SDIN_RAW: DBG3.3, R2.2, U12.2 (A), U14.2 (A), U16.2 (A), U18.2 (A), U20.2 (A), U22.2 (A)
SERIAL_COM1: U10.6 (GPIO4), U26.1 (IO1), U26.4 (D2+), U26.7 (NC), U26.10 (NC), USB2.6 (DP1), USB2.8 (DP2)
SERIAL_COM2: U10.7 (GPIO5), U26.2 (IO2), U26.5 (D2-), U26.6 (NC), U26.9 (NC), USB2.5 (DN2), USB2.7 (DN1)
SR_CLOCK: DBG3.6, U4.11 (SRCLK), U5.11 (SRCLK), U6.11 (SRCLK), U10.39 (GPIO27_ADC1)
SR_DATA: DBG3.7, U4.14 (SER), U10.38 (GPIO26_ADC0)
SR_LATCH: DBG3.8, U4.12 (RCLK), U5.12 (RCLK), U6.12 (RCLK), U10.40 (GPIO28_ADC2)
VBUS: D2.2 (A), R8.1, USB1.2 (VBUS), USB1.11 (VBUS)
VDD: C3_1.1, C3_2.1, C3_3.1, C3_4.1, C3_5.1, C3_6.1, C3_8.1, C3_9.1, C3_10.1, C3_11.1, C3_12.1, C3_13.1, C3_15.1, C3_16.1, C3_17.1, C3_18.1, C3_19.1, C3_20.1, C3_25.1, C3_26.1, C3_27.1, C5.1, C6.1, C9.1, C17.1, C18.1, C19.1, C20.1, C21.1, C22.1, C23.1, C24.1, C26.1, D1.2 (A), DBG3.9, Exp0.6 (GND), J1.7, J2.7, J3.7, J4.7, J5.7, J6.7, J8.7, J9.7, J10.7, J11.7, J12.7, J13.7, J15.7, J16.7, J17.7, J19.7, J20.7, J25.7, J26.7, J27.7, L2.2, R1_1.1, R1_2.1, R1_3.1, R1_4.1, R1_5.1, R1_6.1, R1_8.1, R1_9.1, R1_10.1, R1_11.1, R1_12.1, R1_13.1, R1_15.1, R1_16.1, R1_17.1, R1_18.1, R1_19.1, R1_20.1, R1_25.1, R1_26.1, R1_27.1, R3.1, R4.1, R14.2, R20.1, U2.1 (RUN), U3.4 (EN), U4.16 (VCC), U5.16 (VCC), U6.16 (VCC), U9.8 (VCC), U10.1 (IOVDD), U10.10 (IOVDD), U10.22 (IOVDD), U10.33 (IOVDD), U10.42 (IOVDD), U10.43 (ADC_AVDD), U10.44 (VREG_IN), U10.48 (USB_VDD), U10.49 (IOVDD), U12.5 (VCCB), U13.5 (VCCB), U14.5 (VCCB), U15.5 (VCCB), U16.5 (VCCB), U17.5 (VCCB), U18.5 (VCCB), U19.5 (VCCB), U20.5 (VCCB), U21.5 (VCCB), U22.5 (VCCB), U23.5 (VCCB)
VSUP: C2_1.1, C2_2.1, C2_3.1, C2_4.1, C2_5.1, C2_6.1, C2_8.1, C2_9.1, C2_10.1, C2_11.1, C2_12.1, C2_13.1, C2_15.1, C2_16.1, C2_17.1, C2_18.1, C2_19.1, C2_20.1, C2_25.1, C2_26.1, C2_27.1, DBG3.10, J1.6, J2.6, J3.6, J4.6, J5.6, J6.6, J8.6, J9.6, J10.6, J11.6, J12.6, J13.6, J15.6, J16.6, J17.6, J19.6, J20.6, J25.6, J26.6, J27.6, JP1.2 (C)
VSUP_UNLIMITED: C11.1, C12.1, C13.1, D6.2 (A), JP1.3 (B), L1.2, R10.2, U3.5 (IN)
VSYS: C4.1, C10.1, D2.1 (K), U1.1 (RUN), U1.4 (VDD), U2.4 (VDD), USB2.2 (VBUS), USB2.11 (VBUS)

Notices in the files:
PCBs/Pico-Keyboard_pico_keyboard_v1/raw.kicad_pcb:
CC BY-SA 4.0
